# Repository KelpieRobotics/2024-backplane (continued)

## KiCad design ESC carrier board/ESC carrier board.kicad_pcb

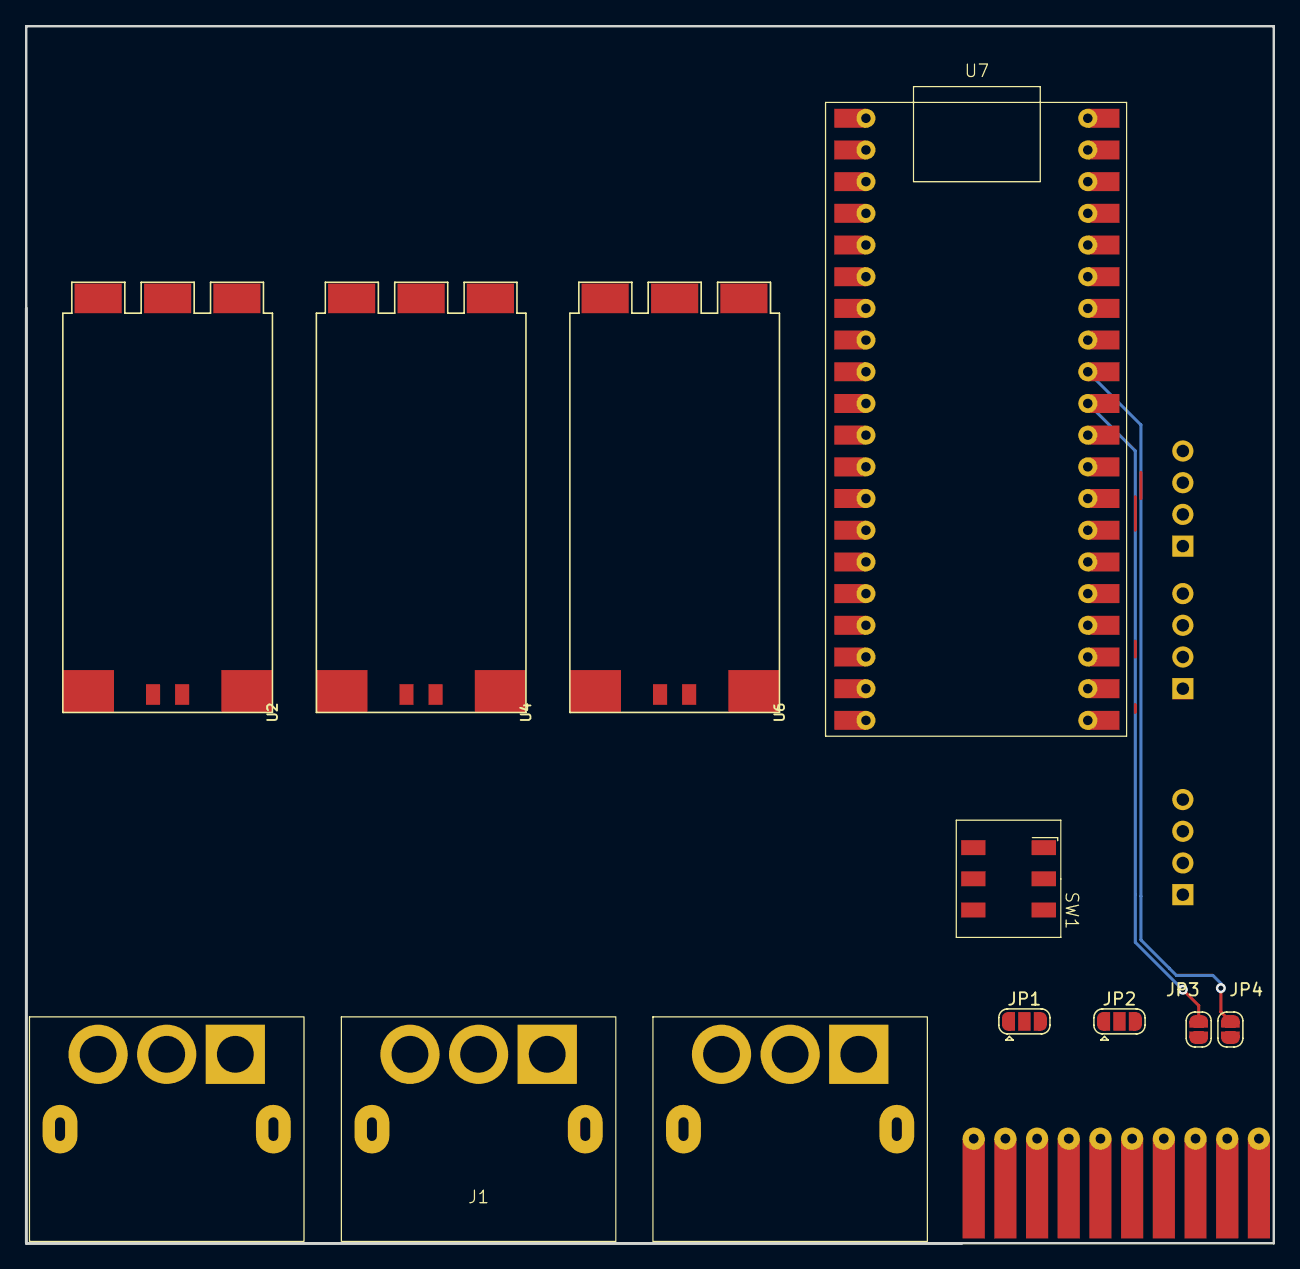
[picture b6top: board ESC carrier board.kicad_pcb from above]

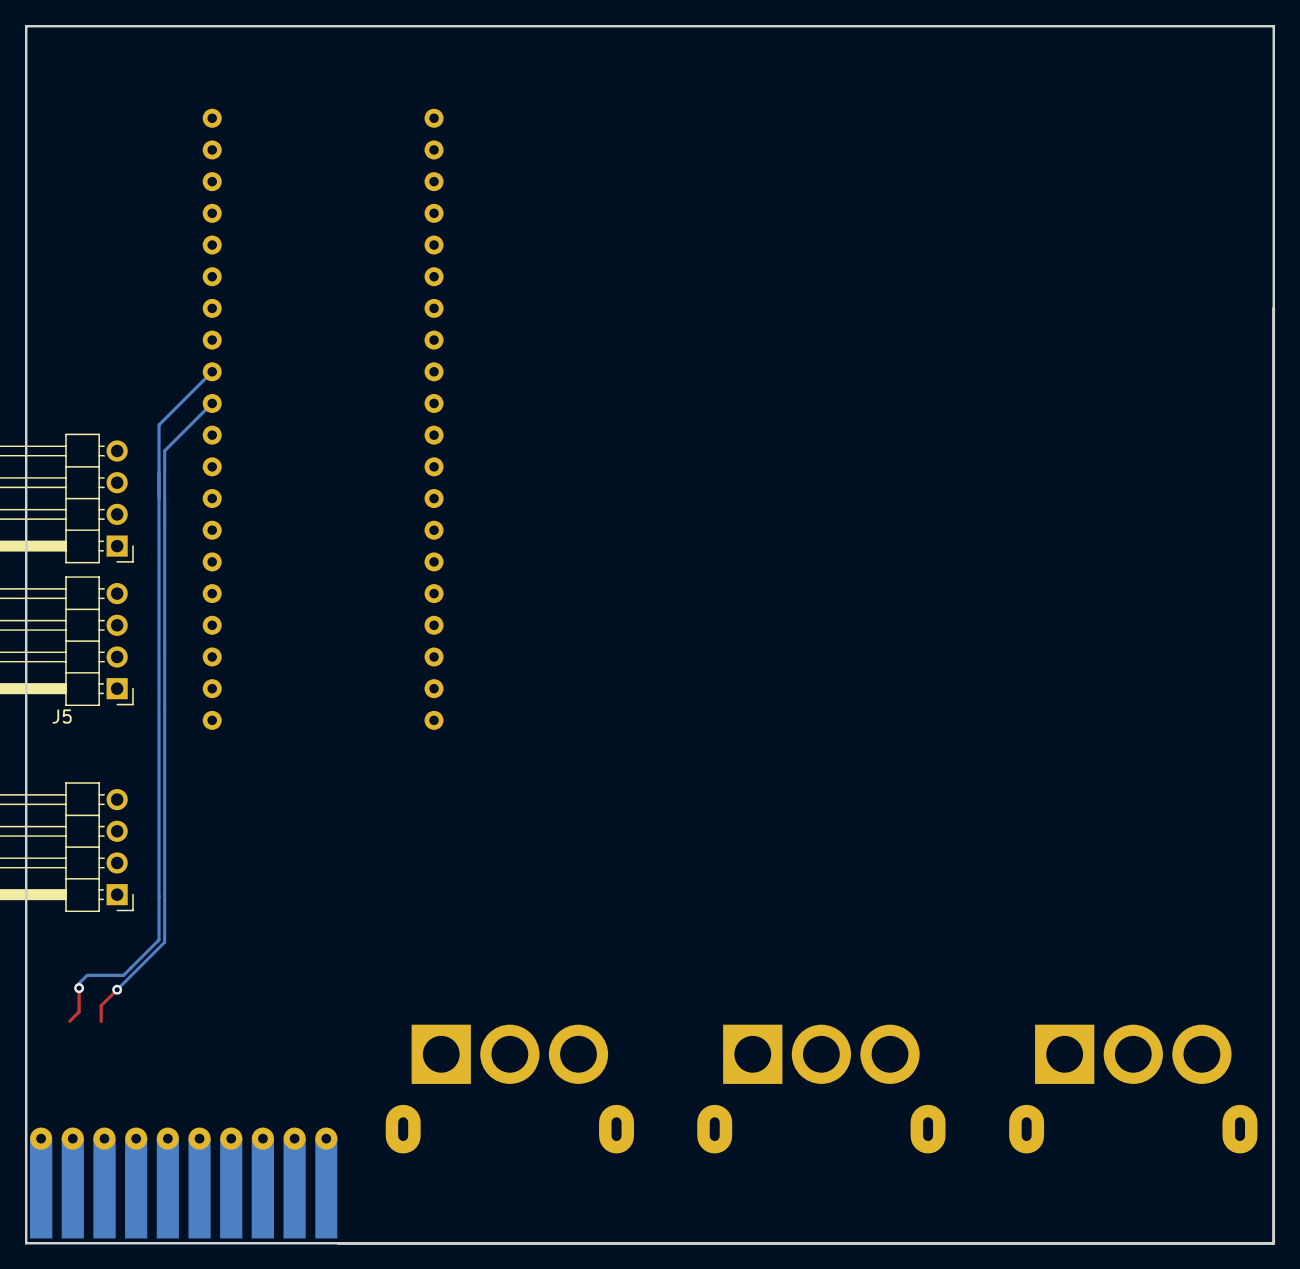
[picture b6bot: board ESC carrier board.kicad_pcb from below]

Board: 2 copper layers, 100.0 x 97.5 mm, 14 parts (3 on the bottom side), 32 nets.

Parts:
J1: MR60PW-M_X3
J2: CardEdge_2x10
J3, J4, J5: Conn_01x04_Pin; PinHeader_1x04_P2.54mm_Horizontal
JP1, JP2: Jumper_3_Open; SolderJumper-3_P1.3mm_Open_RoundedPad1.0x1.5mm
JP3, JP4: Jumper_2_Bridged; SolderJumper-2_P1.3mm_Open_RoundedPad1.0x1.5mm
SW1: SW_DPDT_x2; CUI-Switch-SMD
U2, U4, U6: ESC
U7: ESP32-S3-Pico

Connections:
/5v: J1.9 (5V), U7.39 (VSYS)
/PESC1: J1.4 (12V), U2.+
/PESC2: J1.5 (12V), U4.+
/PESC3: J1.6 (12V), U6.+
/sGP6: J4.2, U6.S, U7.9 (GP6)
/sGP7: J4.3, U4.S, U7.10 (GP7)
/sGP8: J4.4, U2.S, U7.11 (GP8)
/sg: J4.1, U2.G, U4.G, U6.G, U7.13 (GND)
GND: J1.2 (GND), J1.3 (GND), J1.8 (GND), U2.-, U4.-, U6.-, U7.18 (GND)
unnamed: J2.3 (RX0/SCL0), JP2.1 (A)
unnamed: J2.6 (RX1/SCL1), JP2.3 (B)
unnamed: J2.9 (RX2/SCL2), JP4.1 (A)
unnamed: J2.2 (TX0/SDA0), JP1.1 (A)
unnamed: J2.5 (TX1/SDA1), JP1.3 (B)
unnamed: J2.8 (TX2/SDA2), JP3.1 (A)
unnamed: J3.1, U7.8 (GND)
unnamed: J3.2, U7.7 (GP5)
unnamed: J3.3, U7.6 (GP4)
unnamed: J3.4, U7.5 (GP3)
unnamed: J5.1, U7.23 (GND)
unnamed: J5.2, U7.21 (GP16)
unnamed: J5.3, U7.22 (GP17)
unnamed: J5.4, U7.24 (GP18)
unnamed: JP1.2 (C), SW1.2 (B)
unnamed: JP2.2 (C), SW1.5 (B)
RX0: SW1.4 (A), U7.2 (GP1)
SCL0: SW1.6 (C), U7.27 (GP21)
SCL1: JP4.2 (B), U7.32 (GP27)
SDA0: SW1.3 (C), U7.26 (GP20)
SDA1: JP3.2 (B), U7.31 (GP26)
TX0: SW1.1 (A), U7.1 (GP0)
sGND: J2.1 (sGND), J2.4 (sGND), J2.7 (sGND), J2.10 (sGND)

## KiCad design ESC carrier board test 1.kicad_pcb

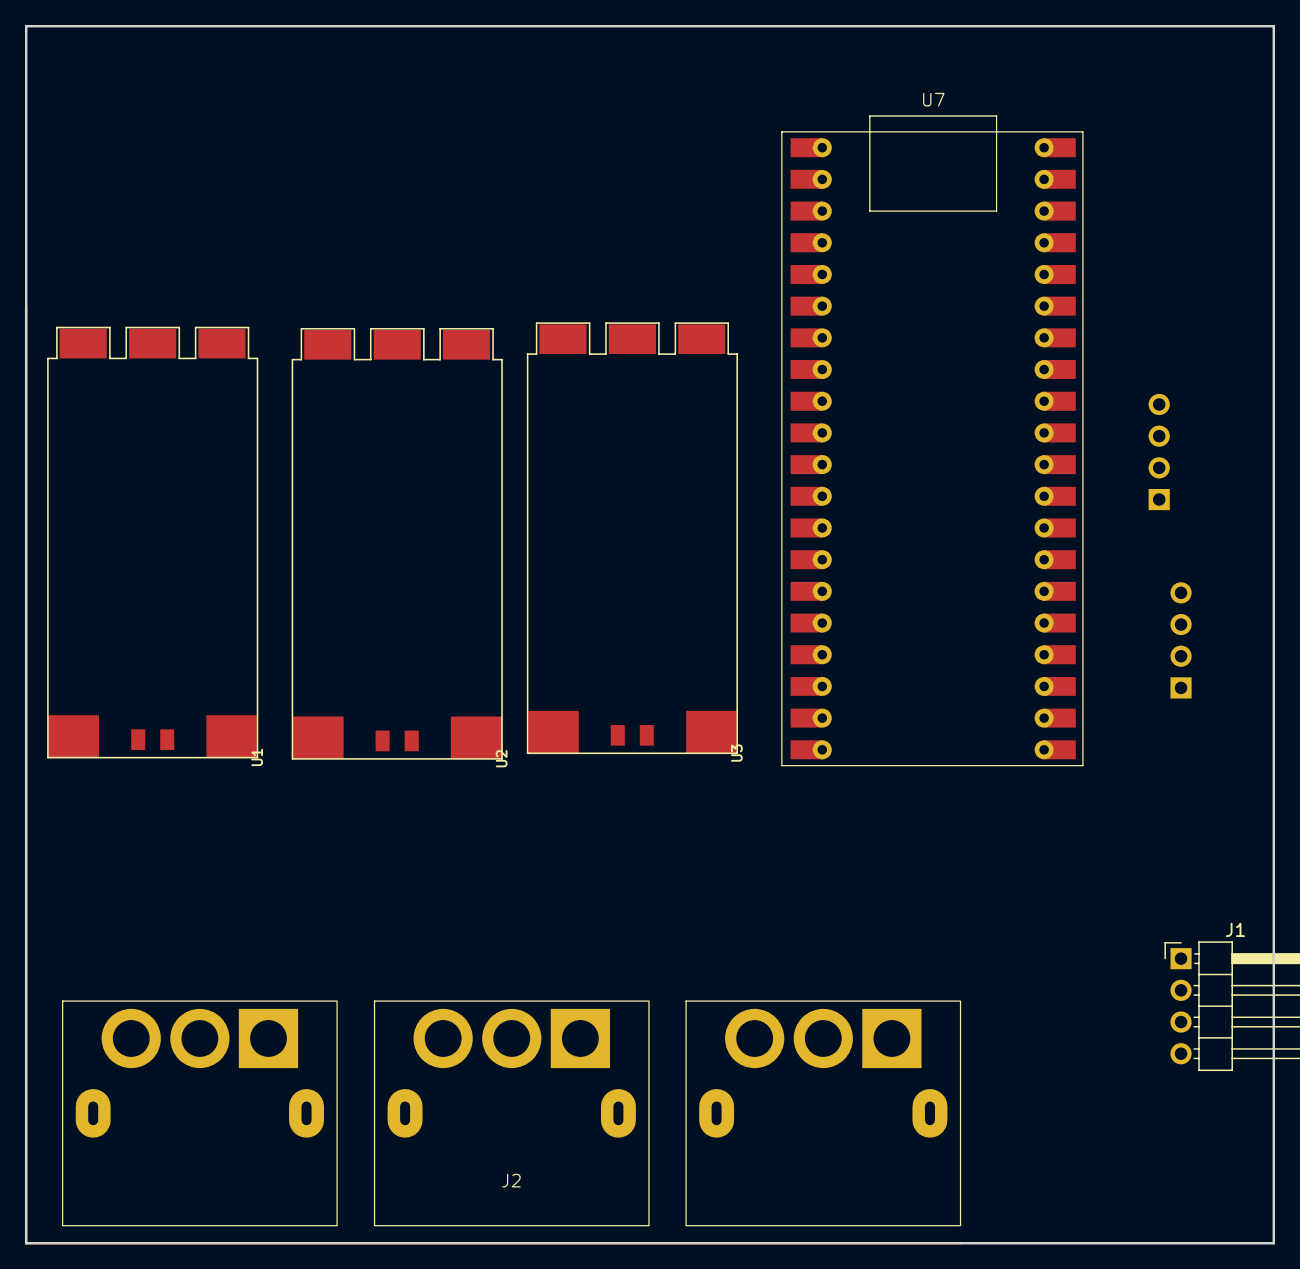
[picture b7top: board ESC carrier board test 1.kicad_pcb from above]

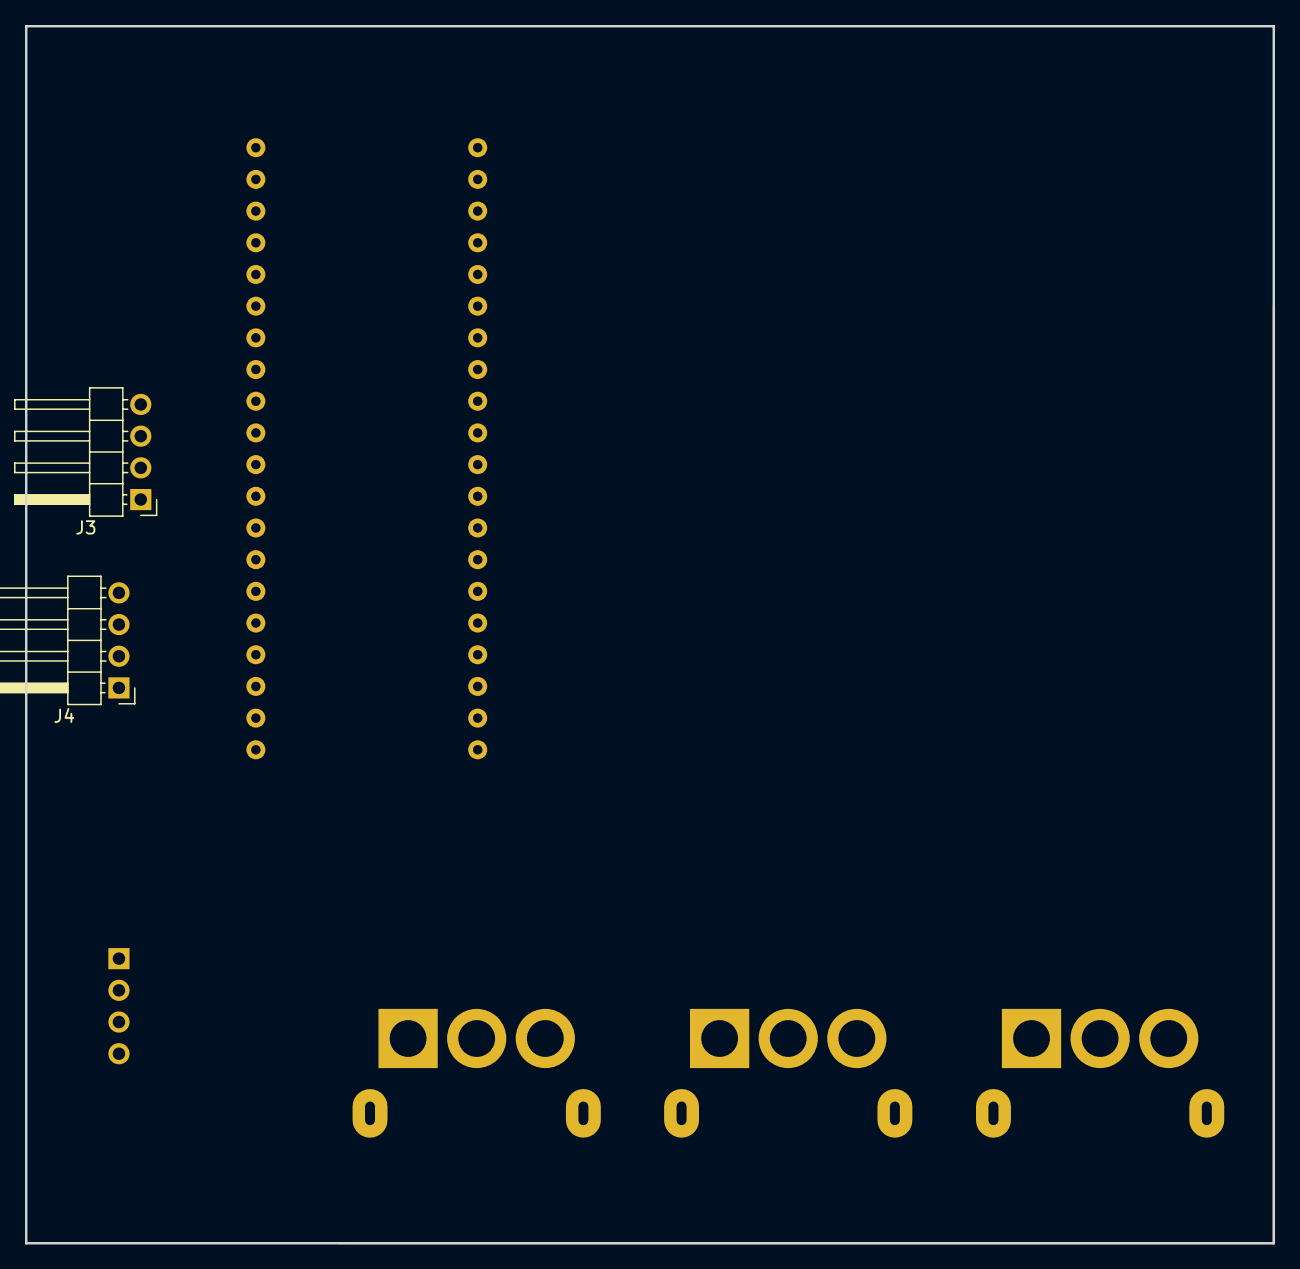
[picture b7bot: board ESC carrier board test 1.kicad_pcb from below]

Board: 2 copper layers, 100.0 x 97.5 mm, 8 parts (2 on the bottom side), 17 nets, no tracks yet.

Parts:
J1, J3, J4: Conn_01x04_Pin; PinHeader_1x04_P2.54mm_Horizontal
J2: MR60PW-M_X3
U1, U2, U3: ESC
U7: ESP32-S3-Pico

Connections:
/5v: J2.9 (C), U7.39 (VSYS)
/GND: J2.2 (B), J2.3 (C), J2.8 (B), U1.-, U2.-, U3.-, U7.18 (GND)
/PESC1: J2.4 (A), U1.+
/PESC2: J2.5 (B), U2.+
/PESC3: J2.6 (C), U3.+
/sGP37: J1.1, U3.S, U7.16 (GP37)
/sGP38: J1.2, U2.S, U7.17 (GP38)
/sg: J1.4, U1.G, U2.G, U3.G, U7.13 (GND)
/signalGP39: J1.3, U1.S, U7.19 (GP39)
unnamed: J3.1, U7.28 (GND)
unnamed: J3.2, U7.29 (GP6)
unnamed: J3.3, U7.31 (GP7)
unnamed: J3.4, U7.32 (GP8)
unnamed: J4.1, U7.23 (GND)
unnamed: J4.2, U7.24 (GP1)
unnamed: J4.3, U7.25 (GP2)
unnamed: J4.4, U7.26 (GP4)

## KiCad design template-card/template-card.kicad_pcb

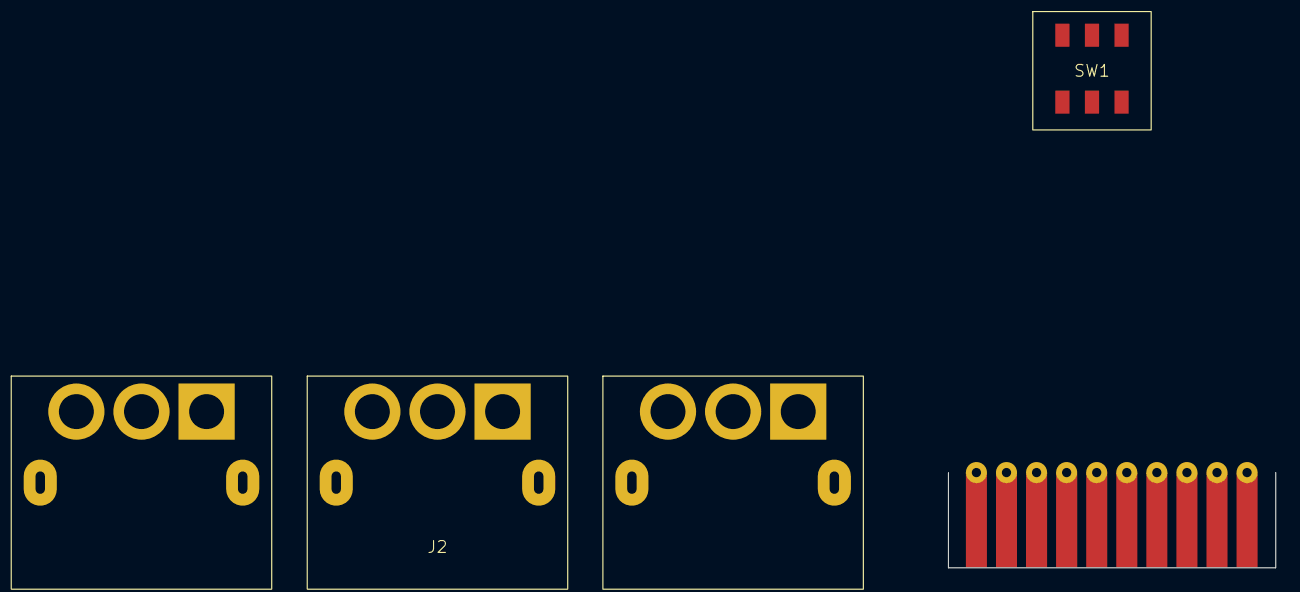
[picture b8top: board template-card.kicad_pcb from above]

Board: 2 copper layers, 3 parts (0 on the bottom side), 5 nets, no tracks yet.

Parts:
J1: Conn_01x10_Pin; CardEdge_2x10
J2: MR60PW-M_X3
SW1: SW_DPDT_x2; SW_CUI_DPDT

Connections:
/12v: J2.4 (A), J2.5 (B), J2.6 (C)
/rx0/scl0: J1.3, SW1.5 (B)
/tx0/sda0: J1.2, SW1.2 (B)
GND1: J1.1, J1.4, J1.7, J1.10
GND2: J2.3 (C), J2.7 (A), J2.9 (C)

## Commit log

2024-02-21 Made the connector symbols for MR60PW-M, MR60-F and the footprints for MR60PW-M, Edge connector
2024-02-21 moved footprint and symbol lib to repo
2024-02-21 made switch footprint
2024-02-22 blergh
2024-02-22 Complete Power Footprints & Symbols
    - Completed the preselected regulator's footprints and symbols
2024-02-26 Added gitignore
2024-02-26 Cleaned up repo
2024-02-26 Partially cleaned up schematic
2024-02-26 Updated Repo
2024-02-27 Minor changes to schematic
2024-03-02 Updated Schematic and components
2024-03-02 Modified board
2024-03-04 template finished
2024-03-04 ahaaaaaaaaaaa
2024-03-04 gitignore
2024-03-04 Added new footprints
2024-03-06 Fixed merge conflicts
2024-03-06 Organization & Start Bus 1 V0.5
    - Started schematic for bus 1
    - Created project file structure
    - TODO can be found in the bus 1 schematic
2024-03-06 esc carrier boards
    updated carrier board pcb, it is not routed yet and some clarification as to what pins to connect to the card edge connector is still required.
2024-03-07 Completed Prelim Board Layout
2024-03-07 Routed board
2024-03-07 Modified board and footprints
2024-03-07 made 3x mr60 f connector
2024-03-07 changed 12v lines to be seperate
2024-03-07 made edac card edge connector footprint
2024-03-07 modified edac edge connector
2024-03-16 modified card edge connector
2024-03-16 duplicate xt90 connector footprint with nums
2024-03-16 backplane schematic
2024-03-16 asdn
2024-03-16 finalized backplane schematic, started pcb layout
2024-03-16 24v complete now to add 5v
2024-03-20 ESC carrier board jumper routing
2024-03-23 Complete 12V
2024-03-23 pushing again
2024-03-23 Designed the 5v voltage regulator
2024-03-24 Complete Power Boards
2024-03-24 modified pcb
2024-03-28 backplane is laid out
2024-03-28 backplane routed
2024-03-28 fixed pad connection on some fills
2024-03-28 48v wasnt properly connected
2024-03-28 changed to mr60PW-M connector
2024-03-28 ground plane
2024-03-29 added 3d models, cleaned up silk screen and added some voltage indicators
2024-03-29 little tweaks
2024-03-29 added xt90 connector
2024-03-29 modified card edge footprint
2024-03-29 changed the card edge connector as per the new specs
2024-03-29 JLC compatibility changes
2024-03-29 changed font thickness and added contributor
2024-03-30 made mr60pw-m mechanical pins a bit smaller
2024-03-30 JLC Design Constraints
2024-03-30 changed card edge connector
2024-04-01 Modified Board for easier ESC mounting
2024-04-02 figured out mounting hole placements
2024-04-02 STEP Exports
2024-04-02 step file created
2024-04-03 added links, tried to do a BOM, modified silkscreen
2024-04-04 added stitching vias
2024-04-04 Shorted I2C
2024-04-05 Updated board from schematic
2024-04-05 Fixed errors on PCB
2024-04-05 Fixed DRC errors
2024-04-05 Bus silkscreens
2024-04-06 gerber file made
2024-04-06 added svg
2024-04-06 bom stuff happening
2024-04-17 Gerbers
